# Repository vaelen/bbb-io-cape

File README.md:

# BeagleBone Black I/O Cape

A KiCad-designed I/O expansion cape for the BeagleBone Black SBC, featuring Grove-compatible connectors for easy interfacing with sensors, actuators, and communication peripherals.

**NOTE: The design has not yet been verified, use at your own risk!**

## Features

| Interface | Connector Count | Notes                             |
|-----------|----------------:|-----------------------------------|
| Analog    |               3 | Grove 4-pin (A1, A2, A3)          |
| Digital   |               9 | Grove 4-pin (D1-D9)               |
| I2C       |               2 | Grove 4-pin (I2C1, I2C2)          |
| UART      |               3 | Grove 4-pin (UART1, UART2, UART4) |

### Onboard Components

- **DS3231MZ** - High-precision real-time clock with CR2032 battery backup
- **CAT24C256** - 256Kb I2C EEPROM for cape identification
- **2-position DIP switch** - Configuration options
- **Test points** - WP (write protect) and GND

## Pinout

The cape connects via the standard BeagleBone Black P8 and P9 expansion headers (2x23 pin, 2.54mm pitch).

### Connectors

| Connector | Pin 1   | Pin 2   | Function            |
|-----------|---------|---------|---------------------|
| UART1     | P9 / 26 | P9 / 24 | UART1 RX / TX       |dtc -@ -I dts -O dtb -o BB-IO-CAPE-00A0.dtbo BB-IO-CAPE-00A0.dts
| UART2     | P9 / 22 | P9 / 21 | UART2 RX / TX       |
| UART4     | P9 / 11 | P9 / 13 | UART4 RX / TX       |
| I2C1      | P9 / 17 | P9 / 18 | I2C1 SCL / SDA      |
| I2C2      | P9 / 19 | P9 / 20 | I2C2 SCL / SDA      |
| A1        | P9 / 39 | P9 / 33 | AIN 0 / AIN 4       |
| A2        | P9 / 37 | P9 / 35 | AIN 2 / AIN 6       |
| A3        | P9 / 38 | P9 / 36 | AIN 3 / AIN 5       |
| D1        | P9 / 42 | P9 / 41 | GPIO 07 / GPIO 116  |
| D2        | P8 / 19 | P8 / 13 | GPIO 22 / GPIO 23   |
| D3        | P8 / 14 | P8 / 17 | GPIO 26 / GPIO 27   |
| D4        | P8 / 12 | P8 / 11 | GPIO 44 / GPIO 45   |
| D5        | P8 / 16 | P8 / 15 | GPIO 46 / GPIO 47   |
| D6        | P9 / 15 | P9 / 16 | GPIO 48 / GPIO 51   |
| D7        | P8 / 7  | P8 / 8  | GPIO 66 / GPIO 67   |
| D8        | P8 / 10 | P8 / 9  | GPIO 68 / GPIO 69   |
| D9        | P9 / 25 | P9 / 27 | GPIO 117 / GPIO 115 |
| RTC       | P9 / 12 | P8 / 28 | GPIO 60 / GPIO 88   |

**Note:** All I/O signals are 3.3V. Do not apply 5V to any I/O pin.

## Real Time Clock

The real time clock is wired into the I2C2 bus as device 0x68.

## Device Tree Overlay

The cape includes a device tree overlay (`BB-IO-CAPE-00A0.dts`) that configures all peripherals for use under Linux.

The filename `BB-IO-CAPE-00A0` matches the part number (`BB-IO-CAPE`) and version (`00A0`) stored in the cape EEPROM, allowing U-Boot to automatically load the overlay at boot.

### Installing the Pre-compiled Overlay

A pre-compiled overlay (`BB-IO-CAPE-00A0.dtbo`) is included. To install on your BeagleBone:

```bash
# Copy the overlay to the firmware directory
sudo cp BB-IO-CAPE-00A0.dtbo /lib/firmware/
```

**Important:** The universal cape overlay and conflicting peripherals must be disabled to avoid pin conflicts. Edit `/boot/uEnv.txt` and make the following changes:

```bash
# Use the standard (non-universal) device tree
dtb=am335x-boneblack.dtb

# Comment out the universal cape enable
#enable_uboot_cape_universal=1

# Disable HDMI and audio (they conflict with GPIO pins)
disable_uboot_overlay_video=1
disable_uboot_overlay_audio=1
```

Then reboot for changes to take effect.

### Compiling from Source (Optional)

If you need to modify the overlay or compile it yourself:

```bash
# Preprocess and compile
cpp -nostdinc -I /usr/src/linux-headers-$(uname -r)/include \
    -undef -x assembler-with-cpp BB-IO-CAPE-00A0.dts | \
    dtc -@ -I dts -O dtb -o BB-IO-CAPE-00A0.dtbo -
```

### What the Overlay Configures

| Peripheral | Configuration                                     |
|------------|---------------------------------------------------|
| UART1      | P9.24 (TX), P9.26 (RX) - `/dev/ttyS1`             |
| UART2      | P9.21 (TX), P9.22 (RX) - `/dev/ttyS2`             |
| UART4      | P9.13 (TX), P9.11 (RX) - `/dev/ttyS4`             |
| I2C1       | P9.17 (SCL), P9.18 (SDA) - `/dev/i2c-1` @ 400kHz  |
| I2C2       | P9.19 (SCL), P9.20 (SDA) - `/dev/i2c-2` @ 400kHz  |
| ADC        | Channels 0, 2, 3, 4, 5, 6 enabled                 |
| DS3231 RTC | I2C2 @ 0x68 - `/dev/rtc1`                         |
| GPIO D1-D9 | 18 pins configured as outputs                     |
| RTC 32KHz  | GPIO 60 (P9.12) - 32KHz clock output              |
| RTC Alarm  | GPIO 88 (P8.28) - Alarm interrupt (active low)    |

### Verifying the Overlay

After loading the overlay, verify the devices are available:

```bash
# Check RTC
ls /dev/rtc*
hwclock -r -f /dev/rtc1

# Check I2C devices
i2cdetect -y -r 1   # I2C1 bus
i2cdetect -y -r 2   # I2C2 bus (should show RTC at 0x68)

# Check UARTs
ls /dev/ttyS*

# Check ADC values
cat /sys/bus/iio/devices/iio:device0/in_voltage0_raw
```

## Manufacturing

Production files (Gerbers, BOM, pick-and-place positions) can be generated using KiCad's fabrication toolkit or found in the `production/` directory.

### BOM Summary

| Component     | Value/Part   | Quantity |
|---------------|--------------|----------|
| Grove 4-pin   | Vertical     | 17       |
| EEPROM        | CAT24C256    | 1        |
| RTC           | DS3231MZ     | 1        |
| Battery       | CR2032       | 1        |
| DIP Switch    | 2-position   | 1        |
| Capacitors    | 100nF 0603   | 2        |
| Resistors     | 10kΩ 0603    | 2        |
| Resistor Array| 10kΩ 4x0603  | 1        |
| Resistor Array| 5.6kΩ 4x0603 | 1        |

## Requirements

- KiCad 8.0 or later
- BeagleBone Black (or compatible: BBB Wireless, BeagleBone AI, etc.)

## License

MIT License

Copyright (c) 2026, Andrew C. Young

Permission is hereby granted, free of charge, to any person obtaining a copy
of this software and associated documentation files (the "Software"), to deal
in the Software without restriction, including without limitation the rights
to use, copy, modify, merge, publish, distribute, sublicense, and/or sell
copies of the Software, and to permit persons to whom the Software is
furnished to do so, subject to the following conditions:

The above copyright notice and this permission notice shall be included in all
copies or substantial portions of the Software.

THE SOFTWARE IS PROVIDED "AS IS", WITHOUT WARRANTY OF ANY KIND, EXPRESS OR
IMPLIED, INCLUDING BUT NOT LIMITED TO THE WARRANTIES OF MERCHANTABILITY,
FITNESS FOR A PARTICULAR PURPOSE AND NONINFRINGEMENT. IN NO EVENT SHALL THE
AUTHORS OR COPYRIGHT HOLDERS BE LIABLE FOR ANY CLAIM, DAMAGES OR OTHER
LIABILITY, WHETHER IN AN ACTION OF CONTRACT, TORT OR OTHERWISE, ARISING FROM,
OUT OF OR IN CONNECTION WITH THE SOFTWARE OR THE USE OR OTHER DEALINGS IN THE
SOFTWARE.

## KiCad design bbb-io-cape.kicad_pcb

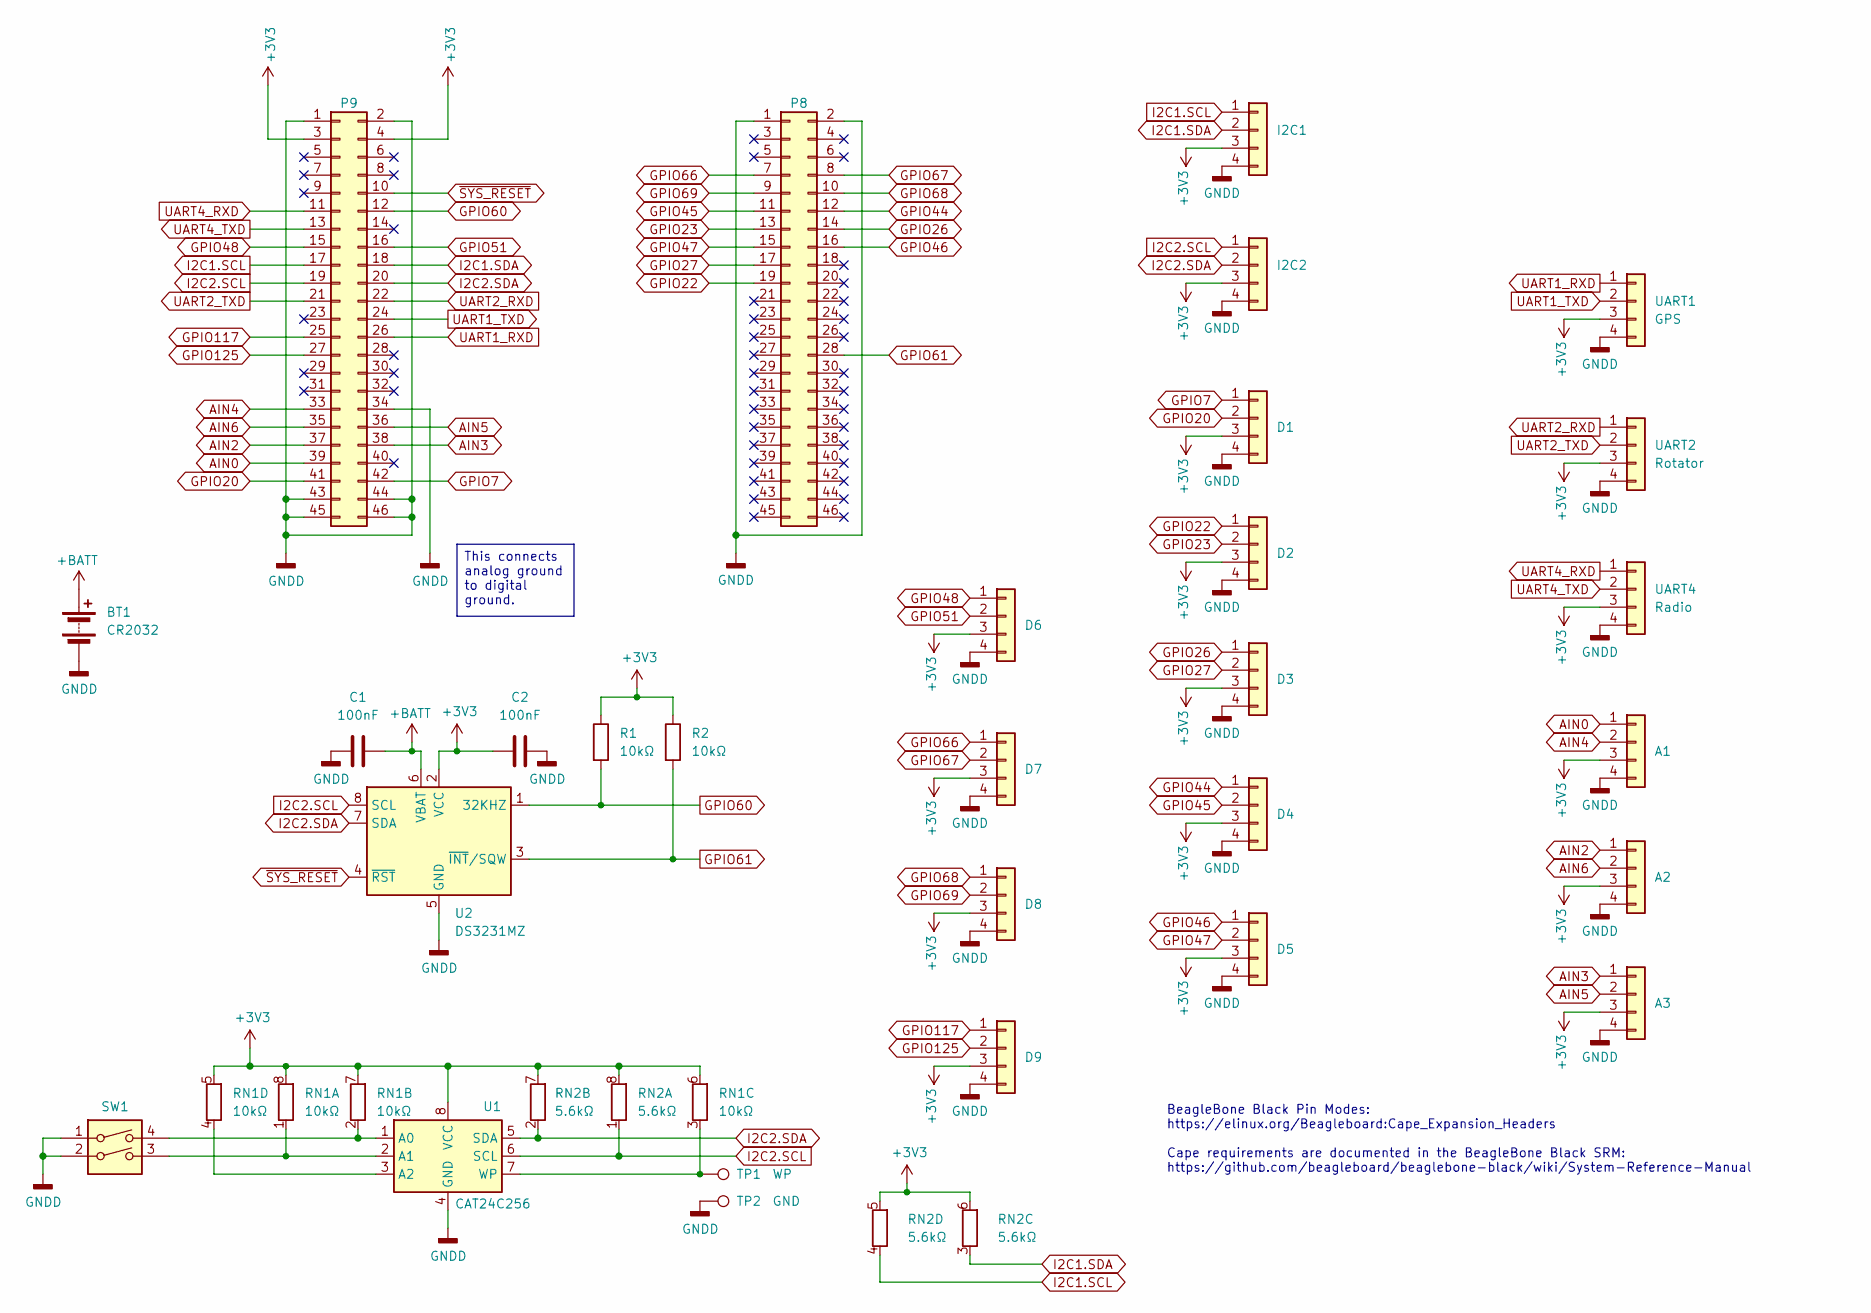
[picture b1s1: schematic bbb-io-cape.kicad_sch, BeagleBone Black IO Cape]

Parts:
A1, A2, A3: NS-Tech_Grove_1x04_P2mm_Vertical; LCSC Part # C5359601
BT1: CR2032; BatteryHolder_Multicomp_BC-2001_1x2032; LCSC Part # C964833
C1, C2: 100nF; C_0603_1608Metric; LCSC Part # C14663
D1, D2, D3, D4, D5, D6, D7, D8, D9: NS-Tech_Grove_1x04_P2mm_Vertical; LCSC Part # C5359601
I2C1, I2C2: NS-Tech_Grove_1x04_P2mm_Vertical; LCSC Part # C5359601
P8, P9: BeagleBone_Black_Header; PinHeader_2x23_P2.54mm_Vertical
R1, R2: 10kΩ; R_0603_1608Metric; LCSC Part # C25804
RN1: 10kΩ; R_Array_Convex_4x0603; LCSC Part # C29718
RN2: 5.6kΩ; R_Array_Convex_4x0603; LCSC Part # C12029
SW1: SW_DIP_x02; SW_DIP_SPSTx02_Slide_6.7x6.64mm_W8.61mm_P2.54mm_LowProfile; LCSC Part # C6331180
TP1: WP; TestPoint_Keystone_5010-5014_Multipurpose; LCSC Part # C2906765
TP2: GND; TestPoint_Keystone_5010-5014_Multipurpose; LCSC Part # C2906765
U1: CAT24C256; SOIC-8-1EP_3.9x4.9mm_P1.27mm_EP2.29x3mm; LCSC Part # C79987
U2: DS3231MZ; SOIC-8_3.9x4.9mm_P1.27mm; LCSC Part # C107410
UART1: GPS; NS-Tech_Grove_1x04_P2mm_Vertical; LCSC Part # C5359601
UART2: Rotator; NS-Tech_Grove_1x04_P2mm_Vertical; LCSC Part # C5359601
UART4: Radio; NS-Tech_Grove_1x04_P2mm_Vertical; LCSC Part # C5359601

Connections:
+3V3: A1.3, A2.3, A3.3, C2.2, D1.3, D2.3, D3.3, D4.3, D5.3, D6.3, D7.3, D8.3, D9.3, I2C1.3, I2C2.3, P9.3, P9.4, R1.1, R2.1, RN1.5 (R4.2), RN1.6 (R3.2), RN1.7 (R2.2), RN1.8 (R1.2), RN2.5 (R4.2), RN2.6 (R3.2), RN2.7 (R2.2), RN2.8 (R1.2), U1.8 (VCC), U2.2 (VCC), UART1.3, UART2.3, UART4.3
+BATT: BT1.1 (+), C1.2, U2.6 (VBAT)
AIN0: A1.1, P9.39
AIN2: A2.1, P9.37
AIN3: A3.1, P9.38
AIN4: A1.2, P9.33
AIN5: A3.2, P9.36
AIN6: A2.2, P9.35
GNDD: A1.4, A2.4, A3.4, BT1.2 (-), C1.1, C2.1, D1.4, D2.4, D3.4, D4.4, D5.4, D6.4, D7.4, D8.4, D9.4, I2C1.4, I2C2.4, P8.1, P8.2, P9.1, P9.2, P9.34, P9.43, P9.44, P9.45, P9.46, SW1.1, SW1.2, TP2.1, U1.4 (GND), U2.5 (GND), UART1.4, UART2.4, UART4.4
GPIO7: D1.1, P9.42
GPIO20: D1.2, P9.41
GPIO22: D2.1, P8.19
GPIO23: D2.2, P8.13
GPIO26: D3.1, P8.14
GPIO27: D3.2, P8.17
GPIO44: D4.1, P8.12
GPIO45: D4.2, P8.11
GPIO46: D5.1, P8.16
GPIO47: D5.2, P8.15
GPIO48: D6.1, P9.15
GPIO51: D6.2, P9.16
GPIO60: P9.12, R1.2, U2.1 (32KHZ)
GPIO61: P8.28, R2.2, U2.3 (~INT/SQW)
GPIO66: D7.1, P8.7
GPIO67: D7.2, P8.8
GPIO68: D8.1, P8.10
GPIO69: D8.2, P8.9
GPIO117: D9.1, P9.25
GPIO125: D9.2, P9.27
I2C1.SCL: I2C1.1, P9.17, RN2.4 (R4.1)
I2C1.SDA: I2C1.2, P9.18, RN2.3 (R3.1)
I2C2.SCL: I2C2.1, P9.19, RN2.1 (R1.1), U1.6 (SCL), U2.8 (SCL)
I2C2.SDA: I2C2.2, P9.20, RN2.2 (R2.1), U1.5 (SDA), U2.7 (SDA)
unnamed: RN1.1 (R1.1), SW1.3, U1.2 (A1)
unnamed: RN1.2 (R2.1), SW1.4, U1.1 (A0)
unnamed: RN1.3 (R3.1), TP1.1, U1.7 (WP)
unnamed: RN1.4 (R4.1), U1.3 (A2)
UART1_RXD: P9.26, UART1.1
UART1_TXD: P9.24, UART1.2
UART2_RXD: P9.22, UART2.1
UART2_TXD: P9.21, UART2.2
UART4_RXD: P9.11, UART4.1
UART4_TXD: P9.13, UART4.2
~SYS_RESET: P9.10, U2.4 (~RST)

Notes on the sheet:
BeagleBone Black Pin Modes: https://elinux.org/Beagleboard:Cape_Expansion_Headers Cape requirements are documented in the BeagleBone Black SRM: https://github.com/beagleboard/beaglebone-black/wiki/System-Reference-Manual
This connects analog ground to digital ground.

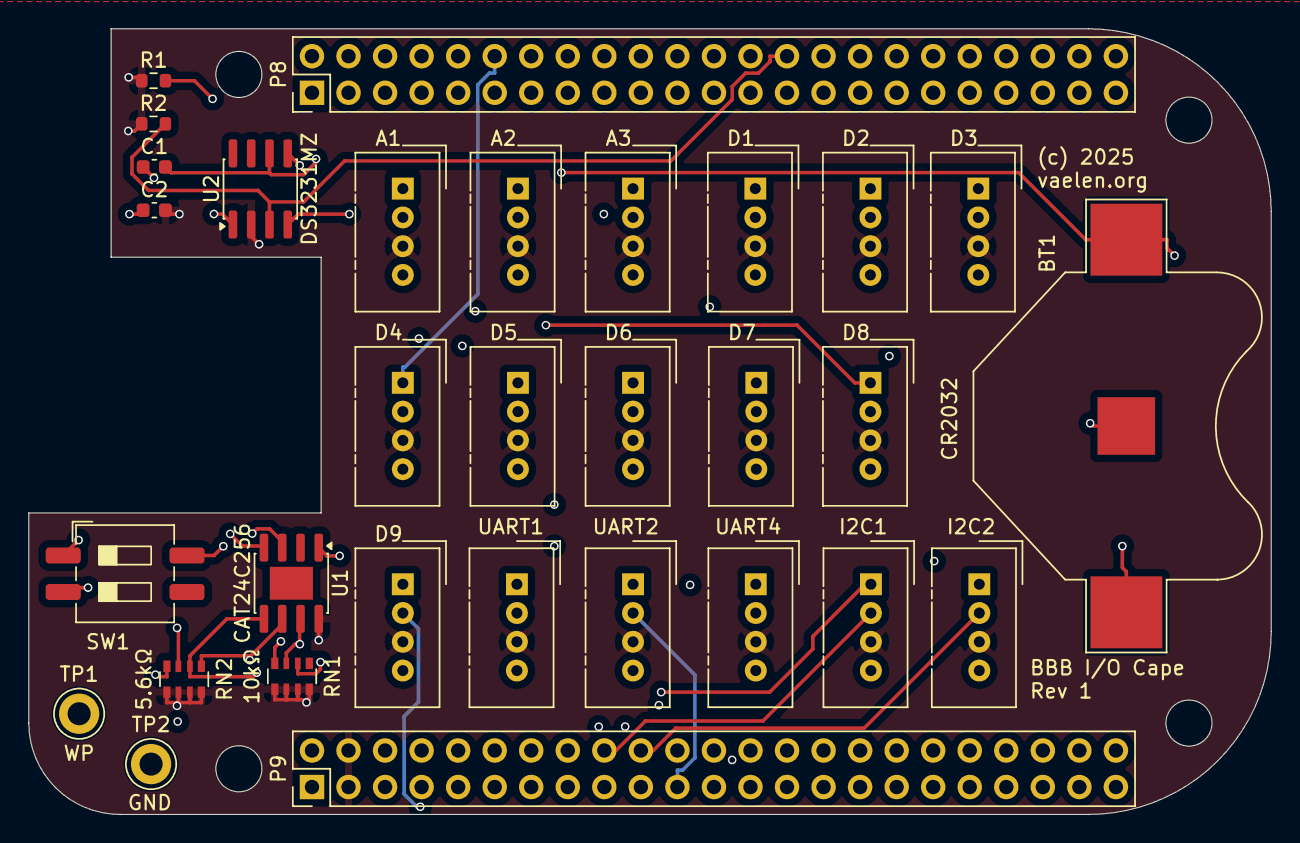
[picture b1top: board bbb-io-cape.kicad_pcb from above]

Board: 4 copper layers, 86.4 x 54.6 mm, 35 parts (0 on the bottom side), 44 nets.

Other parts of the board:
MH1, MH2, MH3, MH4: MountingHole_3.2mm_M3_DIN965

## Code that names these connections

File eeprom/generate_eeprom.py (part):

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    # BB-IO-CAPE Pin Configuration (from README.md)
    #
    # UART1: P9/26 (RX), P9/24 (TX) - Mode 0
    set_pin(9, 26, mux_mode=0, rx_enable=True)   # UART1_RXD
    set_pin(9, 24, mux_mode=0)                    # UART1_TXD

    # UART2: P9/22 (RX), P9/21 (TX) - Mode 1
    set_pin(9, 22, mux_mode=1, rx_enable=True)   # UART2_RXD
    set_pin(9, 21, mux_mode=1)                    # UART2_TXD

    # UART4: P9/11 (RX), P9/13 (TX) - Mode 6
    set_pin(9, 11, mux_mode=6, rx_enable=True)   # UART4_RXD
    set_pin(9, 13, mux_mode=6)                    # UART4_TXD

    # I2C1: P9/17 (SCL), P9/18 (SDA) - Mode 2
    set_pin(9, 17, mux_mode=2, rx_enable=True)   # I2C1_SCL
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
    # Analog inputs (A1, A2, A3) - these only use bit 15 (used flag)
    # A1: P9/39 (AIN0), P9/33 (AIN4)
    set_pin(9, 39, mux_mode=0)  # AIN0
    set_pin(9, 33, mux_mode=0)  # AIN4
    # A2: P9/37 (AIN2), P9/35 (AIN6)
    set_pin(9, 37, mux_mode=0)  # AIN2
    set_pin(9, 35, mux_mode=0)  # AIN6
    # A3: P9/38 (AIN3), P9/36 (AIN5)
    set_pin(9, 38, mux_mode=0)  # AIN3
    set_pin(9, 36, mux_mode=0)  # AIN5

    # Digital GPIO connectors (D1-D9) - Mode 7 (GPIO)
    # D1: P9/42 (GPIO 07), P9/41 (GPIO 116)
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
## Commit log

2026-01-21 Updated license, added pinout, added a tool to generate the eeprom image.
2026-01-21 Small bugfixes.
2026-01-21 Updated EEPROM and added device overlay for Linux.

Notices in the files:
bbb-io-cape.kicad_pcb:
(c) 2025
